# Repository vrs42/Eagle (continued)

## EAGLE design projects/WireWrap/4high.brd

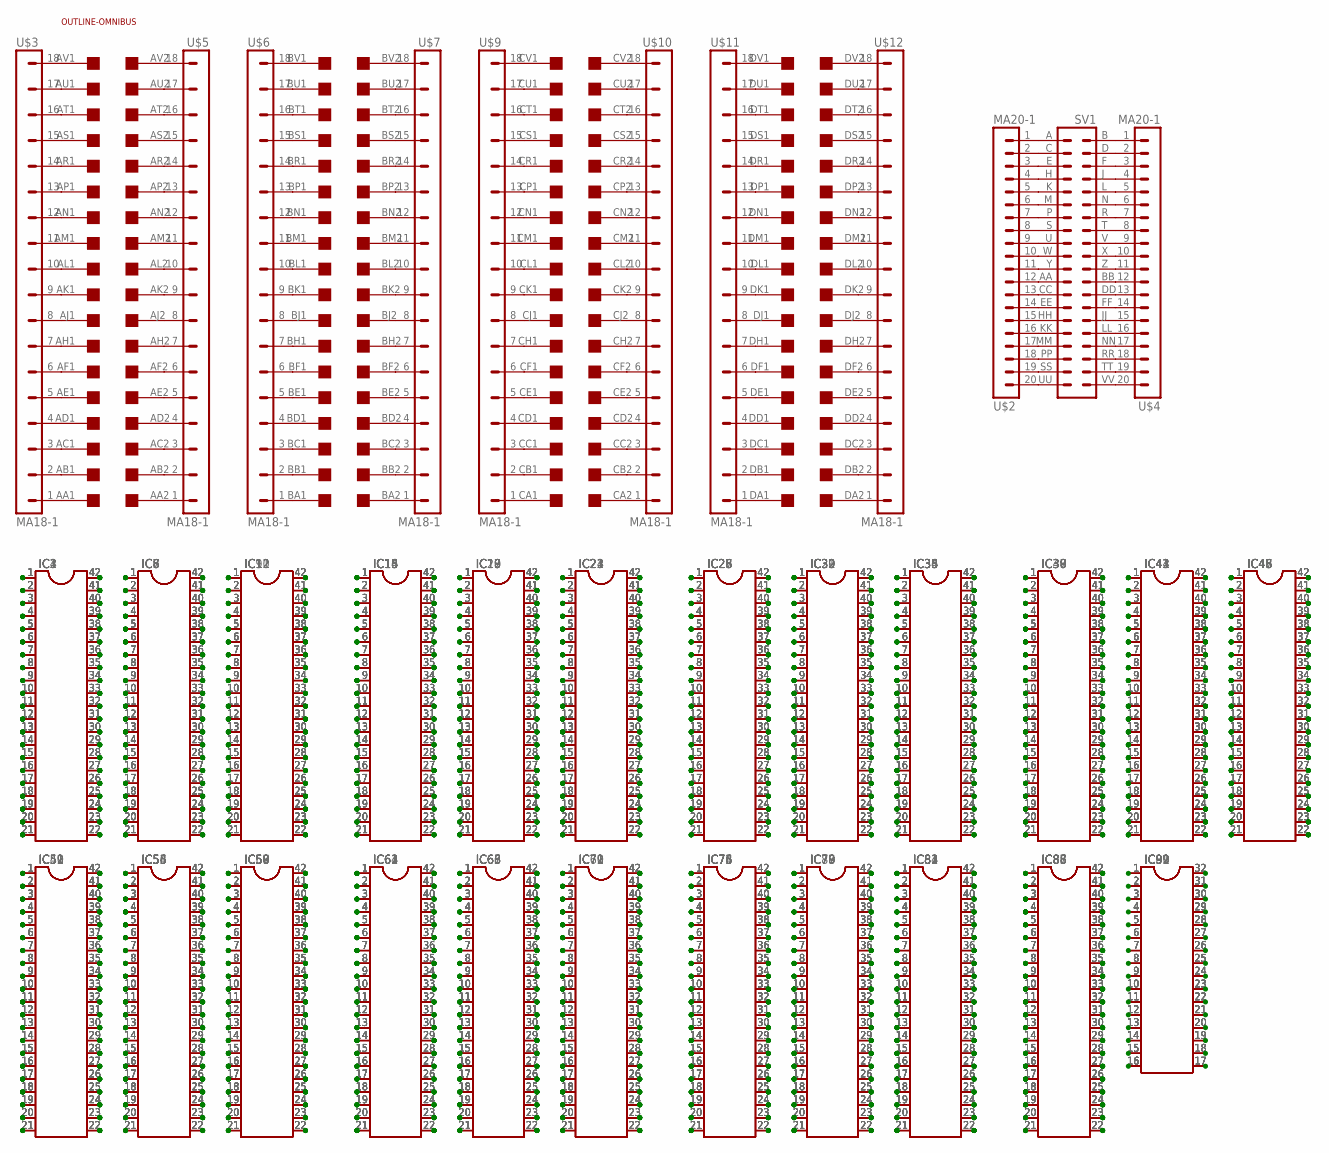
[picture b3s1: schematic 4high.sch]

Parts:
IC1, IC2, IC3, IC4, IC5, IC6, IC7, IC8, IC9, IC10, IC11, IC12, IC13, IC14, IC15, IC16, IC17, IC18, IC19, IC20, IC21, IC22, IC23, IC24, IC25, IC26, IC27, IC28, IC29, IC30, IC31, IC32, IC33, IC34, IC35, IC36, IC37, IC38, IC39, IC40, IC41, IC42, IC43, IC44, IC45, IC46, IC47, IC48, IC49, IC50, IC51, IC52, IC53, IC54, IC55, IC56, IC57, IC58, IC59, IC60, IC61, IC62, IC63, IC64, IC65, IC66, IC67, IC68, IC69, IC70, IC71, IC72, IC73, IC74, IC75, IC76, IC77, IC78, IC79, IC80, IC81, IC82, IC83, IC84, IC85, IC86, IC87, IC88: DIL42
IC89, IC90, IC91, IC92: DIL32
SV1: DEC40PINH
U$1: QUAD; EDGE-CON8
U$2, U$4: MA20-1
U$3, U$5, U$6, U$7, U$9, U$10, U$11, U$12: MA18-1
U$8: OUTLINE-OMNIBUS; OMNIBUS

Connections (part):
GND: U$1.AC2, U$5.3
unnamed: IC1.1, IC2.1, IC3.1, IC4.1
unnamed: IC1.2, IC2.2, IC3.2, IC4.2
unnamed: IC1.3, IC2.3, IC3.3, IC4.3
unnamed: IC1.4, IC2.4, IC3.4, IC4.4
unnamed: IC1.5, IC2.5, IC3.5, IC4.5
unnamed: IC1.6, IC2.6, IC3.6, IC4.6
unnamed: IC1.7, IC2.7, IC3.7, IC4.7
unnamed: IC1.8, IC2.8, IC3.8, IC4.8
unnamed: IC1.9, IC2.9, IC3.9, IC4.9
unnamed: IC1.10, IC2.10, IC3.10, IC4.10
unnamed: IC1.11, IC2.11, IC3.11, IC4.11
unnamed: IC1.12, IC2.12, IC3.12, IC4.12
unnamed: IC1.13, IC2.13, IC3.13, IC4.13
unnamed: IC1.14, IC2.14, IC3.14, IC4.14
unnamed: IC1.15, IC2.15, IC3.15, IC4.15
unnamed: IC1.16, IC2.16, IC3.16, IC4.16
unnamed: IC1.17, IC2.17, IC3.17, IC4.17
unnamed: IC1.18, IC2.18, IC3.18, IC4.18
unnamed: IC1.19, IC2.19, IC3.19, IC4.19
unnamed: IC1.20, IC2.20, IC3.20, IC4.20
unnamed: IC1.21, IC2.21, IC3.21, IC4.21
unnamed: IC1.22, IC2.22, IC3.22, IC4.22
unnamed: IC1.23, IC2.23, IC3.23, IC4.23
unnamed: IC1.24, IC2.24, IC3.24, IC4.24
unnamed: IC1.25, IC2.25, IC3.25, IC4.25
unnamed: IC1.26, IC2.26, IC3.26, IC4.26
unnamed: IC1.27, IC2.27, IC3.27, IC4.27
unnamed: IC1.28, IC2.28, IC3.28, IC4.28
unnamed: IC1.29, IC2.29, IC3.29, IC4.29
unnamed: IC1.30, IC2.30, IC3.30, IC4.30
unnamed: IC1.31, IC2.31, IC3.31, IC4.31
unnamed: IC1.32, IC2.32, IC3.32, IC4.32
unnamed: IC1.33, IC2.33, IC3.33, IC4.33
unnamed: IC1.34, IC2.34, IC3.34, IC4.34
unnamed: IC1.35, IC2.35, IC3.35, IC4.35
unnamed: IC1.36, IC2.36, IC3.36, IC4.36
unnamed: IC1.37, IC2.37, IC3.37, IC4.37
unnamed: IC1.38, IC2.38, IC3.38, IC4.38
unnamed: IC1.39, IC2.39, IC3.39, IC4.39
unnamed: IC1.40, IC2.40, IC3.40, IC4.40
unnamed: IC1.41, IC2.41, IC3.41, IC4.41
unnamed: IC1.42, IC2.42, IC3.42, IC4.42
unnamed: IC5.1, IC6.1, IC7.1, IC8.1
unnamed: IC5.2, IC6.2, IC7.2, IC8.2
unnamed: IC5.3, IC6.3, IC7.3, IC8.3
unnamed: IC5.4, IC6.4, IC7.4, IC8.4
unnamed: IC5.5, IC6.5, IC7.5, IC8.5
unnamed: IC5.6, IC6.6, IC7.6, IC8.6
unnamed: IC5.7, IC6.7, IC7.7, IC8.7
unnamed: IC5.8, IC6.8, IC7.8, IC8.8
unnamed: IC5.9, IC6.9, IC7.9, IC8.9
unnamed: IC5.10, IC6.10, IC7.10, IC8.10
unnamed: IC5.11, IC6.11, IC7.11, IC8.11
unnamed: IC5.12, IC6.12, IC7.12, IC8.12
unnamed: IC5.13, IC6.13, IC7.13, IC8.13
unnamed: IC5.14, IC6.14, IC7.14, IC8.14
unnamed: IC5.15, IC6.15, IC7.15, IC8.15
unnamed: IC5.16, IC6.16, IC7.16, IC8.16
unnamed: IC5.17, IC6.17, IC7.17, IC8.17
unnamed: IC5.18, IC6.18, IC7.18, IC8.18
unnamed: IC5.19, IC6.19, IC7.19, IC8.19
unnamed: IC5.20, IC6.20, IC7.20, IC8.20
unnamed: IC5.21, IC6.21, IC7.21, IC8.21
unnamed: IC5.22, IC6.22, IC7.22, IC8.22
unnamed: IC5.23, IC6.23, IC7.23, IC8.23
unnamed: IC5.24, IC6.24, IC7.24, IC8.24
unnamed: IC5.25, IC6.25, IC7.25, IC8.25
unnamed: IC5.26, IC6.26, IC7.26, IC8.26
unnamed: IC5.27, IC6.27, IC7.27, IC8.27
unnamed: IC5.28, IC6.28, IC7.28, IC8.28
unnamed: IC5.29, IC6.29, IC7.29, IC8.29
unnamed: IC5.30, IC6.30, IC7.30, IC8.30
unnamed: IC5.31, IC6.31, IC7.31, IC8.31
unnamed: IC5.32, IC6.32, IC7.32, IC8.32
unnamed: IC5.33, IC6.33, IC7.33, IC8.33
unnamed: IC5.34, IC6.34, IC7.34, IC8.34
unnamed: IC5.35, IC6.35, IC7.35, IC8.35
unnamed: IC5.36, IC6.36, IC7.36, IC8.36
unnamed: IC5.37, IC6.37, IC7.37, IC8.37
unnamed: IC5.38, IC6.38, IC7.38, IC8.38
unnamed: IC5.39, IC6.39, IC7.39, IC8.39
unnamed: IC5.40, IC6.40, IC7.40, IC8.40
unnamed: IC5.41, IC6.41, IC7.41, IC8.41
unnamed: IC5.42, IC6.42, IC7.42, IC8.42
unnamed: IC9.1, IC10.1, IC11.1, IC12.1
unnamed: IC9.2, IC10.2, IC11.2, IC12.2
unnamed: IC9.3, IC10.3, IC11.3, IC12.3
unnamed: IC9.4, IC10.4, IC11.4, IC12.4
unnamed: IC9.5, IC10.5, IC11.5, IC12.5
unnamed: IC9.6, IC10.6, IC11.6, IC12.6
unnamed: IC9.7, IC10.7, IC11.7, IC12.7
unnamed: IC9.8, IC10.8, IC11.8, IC12.8
unnamed: IC9.9, IC10.9, IC11.9, IC12.9
unnamed: IC9.10, IC10.10, IC11.10, IC12.10
unnamed: IC9.11, IC10.11, IC11.11, IC12.11
unnamed: IC9.12, IC10.12, IC11.12, IC12.12
unnamed: IC9.13, IC10.13, IC11.13, IC12.13
unnamed: IC9.14, IC10.14, IC11.14, IC12.14
unnamed: IC9.15, IC10.15, IC11.15, IC12.15
unnamed: IC9.16, IC10.16, IC11.16, IC12.16
unnamed: IC9.17, IC10.17, IC11.17, IC12.17
unnamed: IC9.18, IC10.18, IC11.18, IC12.18
unnamed: IC9.19, IC10.19, IC11.19, IC12.19
unnamed: IC9.20, IC10.20, IC11.20, IC12.20
unnamed: IC9.21, IC10.21, IC11.21, IC12.21
unnamed: IC9.22, IC10.22, IC11.22, IC12.22
unnamed: IC9.23, IC10.23, IC11.23, IC12.23
unnamed: IC9.24, IC10.24, IC11.24, IC12.24
unnamed: IC9.25, IC10.25, IC11.25, IC12.25
unnamed: IC9.26, IC10.26, IC11.26, IC12.26
unnamed: IC9.27, IC10.27, IC11.27, IC12.27
unnamed: IC9.28, IC10.28, IC11.28, IC12.28
unnamed: IC9.29, IC10.29, IC11.29, IC12.29
unnamed: IC9.30, IC10.30, IC11.30, IC12.30
unnamed: IC9.31, IC10.31, IC11.31, IC12.31
unnamed: IC9.32, IC10.32, IC11.32, IC12.32
unnamed: IC9.33, IC10.33, IC11.33, IC12.33
unnamed: IC9.34, IC10.34, IC11.34, IC12.34
unnamed: IC9.35, IC10.35, IC11.35, IC12.35
unnamed: IC9.36, IC10.36, IC11.36, IC12.36
unnamed: IC9.37, IC10.37, IC11.37, IC12.37
unnamed: IC9.38, IC10.38, IC11.38, IC12.38
unnamed: IC9.39, IC10.39, IC11.39, IC12.39
unnamed: IC9.40, IC10.40, IC11.40, IC12.40
unnamed: IC9.41, IC10.41, IC11.41, IC12.41
unnamed: IC9.42, IC10.42, IC11.42, IC12.42
unnamed: IC13.1, IC14.1, IC15.1, IC16.1
unnamed: IC13.2, IC14.2, IC15.2, IC16.2
unnamed: IC13.3, IC14.3, IC15.3, IC16.3
unnamed: IC13.4, IC14.4, IC15.4, IC16.4
unnamed: IC13.5, IC14.5, IC15.5, IC16.5
unnamed: IC13.6, IC14.6, IC15.6, IC16.6
unnamed: IC13.7, IC14.7, IC15.7, IC16.7
unnamed: IC13.8, IC14.8, IC15.8, IC16.8
unnamed: IC13.9, IC14.9, IC15.9, IC16.9
unnamed: IC13.10, IC14.10, IC15.10, IC16.10
unnamed: IC13.11, IC14.11, IC15.11, IC16.11
unnamed: IC13.12, IC14.12, IC15.12, IC16.12
unnamed: IC13.13, IC14.13, IC15.13, IC16.13
unnamed: IC13.14, IC14.14, IC15.14, IC16.14
unnamed: IC13.15, IC14.15, IC15.15, IC16.15
unnamed: IC13.16, IC14.16, IC15.16, IC16.16
unnamed: IC13.17, IC14.17, IC15.17, IC16.17
unnamed: IC13.18, IC14.18, IC15.18, IC16.18
unnamed: IC13.19, IC14.19, IC15.19, IC16.19
unnamed: IC13.20, IC14.20, IC15.20, IC16.20
unnamed: IC13.21, IC14.21, IC15.21, IC16.21
unnamed: IC13.22, IC14.22, IC15.22, IC16.22
unnamed: IC13.23, IC14.23, IC15.23, IC16.23
unnamed: IC13.24, IC14.24, IC15.24, IC16.24
unnamed: IC13.25, IC14.25, IC15.25, IC16.25
unnamed: IC13.26, IC14.26, IC15.26, IC16.26
unnamed: IC13.27, IC14.27, IC15.27, IC16.27
unnamed: IC13.28, IC14.28, IC15.28, IC16.28
unnamed: IC13.29, IC14.29, IC15.29, IC16.29
unnamed: IC13.30, IC14.30, IC15.30, IC16.30
unnamed: IC13.31, IC14.31, IC15.31, IC16.31
unnamed: IC13.32, IC14.32, IC15.32, IC16.32
unnamed: IC13.33, IC14.33, IC15.33, IC16.33
unnamed: IC13.34, IC14.34, IC15.34, IC16.34
unnamed: IC13.35, IC14.35, IC15.35, IC16.35
unnamed: IC13.36, IC14.36, IC15.36, IC16.36
unnamed: IC13.37, IC14.37, IC15.37, IC16.37
unnamed: IC13.38, IC14.38, IC15.38, IC16.38
unnamed: IC13.39, IC14.39, IC15.39, IC16.39
unnamed: IC13.40, IC14.40, IC15.40, IC16.40
unnamed: IC13.41, IC14.41, IC15.41, IC16.41
unnamed: IC13.42, IC14.42, IC15.42, IC16.42
unnamed: U$1.AK1, U$3.9
unnamed: U$1.AL1, U$3.10
unnamed: U$1.AM1, U$3.11
unnamed: U$1.AN1, U$3.12
unnamed: U$1.AP1, U$3.13
unnamed: U$1.AR1, U$3.14
unnamed: U$1.AS1, U$3.15
unnamed: U$1.AT1, U$3.16
unnamed: U$1.AU1, U$3.17
unnamed: U$1.AV1, U$3.18
unnamed: U$1.AJ1, U$3.8
unnamed: U$1.AH1, U$3.7
unnamed: U$1.AF1, U$3.6
unnamed: U$1.AE1, U$3.5
unnamed: U$1.AD1, U$3.4
unnamed: U$1.AC1, U$3.3
unnamed: U$1.AB1, U$3.2
unnamed: U$1.AA1, U$3.1
unnamed: U$1.AL2, U$5.10
unnamed: U$1.AM2, U$5.11
unnamed: U$1.AN2, U$5.12
unnamed: U$1.AP2, U$5.13
unnamed: U$1.AR2, U$5.14
unnamed: U$1.AS2, U$5.15
unnamed: U$1.AT2, U$5.16
unnamed: U$1.AK2, U$5.9
unnamed: U$1.AJ2, U$5.8
unnamed: U$1.AH2, U$5.7
unnamed: U$1.AF2, U$5.6
unnamed: U$1.AE2, U$5.5
unnamed: U$1.AD2, U$5.4
unnamed: IC17.1, IC18.1, IC19.1, IC20.1
unnamed: U$1.AU2, U$5.17
unnamed: U$1.AV2, U$5.18
unnamed: U$1.AB2, U$5.2
unnamed: IC17.2, IC18.2, IC19.2, IC20.2
unnamed: IC17.3, IC18.3, IC19.3, IC20.3
unnamed: IC17.4, IC18.4, IC19.4, IC20.4
unnamed: IC17.5, IC18.5, IC19.5, IC20.5
unnamed: IC17.6, IC18.6, IC19.6, IC20.6
unnamed: IC17.7, IC18.7, IC19.7, IC20.7
unnamed: IC17.8, IC18.8, IC19.8, IC20.8
unnamed: IC17.9, IC18.9, IC19.9, IC20.9
unnamed: IC17.10, IC18.10, IC19.10, IC20.10
unnamed: IC17.11, IC18.11, IC19.11, IC20.11
unnamed: IC17.12, IC18.12, IC19.12, IC20.12
unnamed: IC17.13, IC18.13, IC19.13, IC20.13
unnamed: IC17.14, IC18.14, IC19.14, IC20.14
unnamed: IC17.15, IC18.15, IC19.15, IC20.15
unnamed: IC17.16, IC18.16, IC19.16, IC20.16
unnamed: IC17.17, IC18.17, IC19.17, IC20.17
unnamed: IC17.18, IC18.18, IC19.18, IC20.18
unnamed: IC17.19, IC18.19, IC19.19, IC20.19
unnamed: IC17.20, IC18.20, IC19.20, IC20.20
unnamed: IC17.21, IC18.21, IC19.21, IC20.21
unnamed: IC17.22, IC18.22, IC19.22, IC20.22
unnamed: IC17.23, IC18.23, IC19.23, IC20.23
unnamed: IC17.24, IC18.24, IC19.24, IC20.24
unnamed: IC17.25, IC18.25, IC19.25, IC20.25
unnamed: IC17.26, IC18.26, IC19.26, IC20.26
unnamed: IC17.27, IC18.27, IC19.27, IC20.27
unnamed: IC17.28, IC18.28, IC19.28, IC20.28
unnamed: IC17.29, IC18.29, IC19.29, IC20.29
unnamed: IC17.30, IC18.30, IC19.30, IC20.30
unnamed: IC17.31, IC18.31, IC19.31, IC20.31
unnamed: IC17.32, IC18.32, IC19.32, IC20.32
unnamed: IC17.33, IC18.33, IC19.33, IC20.33
unnamed: IC17.34, IC18.34, IC19.34, IC20.34
unnamed: IC17.35, IC18.35, IC19.35, IC20.35
unnamed: IC17.36, IC18.36, IC19.36, IC20.36
unnamed: IC17.37, IC18.37, IC19.37, IC20.37
unnamed: IC17.38, IC18.38, IC19.38, IC20.38
unnamed: IC17.39, IC18.39, IC19.39, IC20.39
unnamed: IC17.40, IC18.40, IC19.40, IC20.40
unnamed: IC17.41, IC18.41, IC19.41, IC20.41
unnamed: IC17.42, IC18.42, IC19.42, IC20.42
unnamed: IC21.1, IC22.1, IC23.1, IC24.1
unnamed: IC21.2, IC22.2, IC23.2, IC24.2
unnamed: IC21.3, IC22.3, IC23.3, IC24.3
unnamed: IC21.4, IC22.4, IC23.4, IC24.4
unnamed: IC21.5, IC22.5, IC23.5, IC24.5
unnamed: IC21.6, IC22.6, IC23.6, IC24.6
unnamed: IC21.7, IC22.7, IC23.7, IC24.7
unnamed: IC21.8, IC22.8, IC23.8, IC24.8
unnamed: IC21.9, IC22.9, IC23.9, IC24.9
unnamed: IC21.10, IC22.10, IC23.10, IC24.10
unnamed: IC21.11, IC22.11, IC23.11, IC24.11
unnamed: IC21.12, IC22.12, IC23.12, IC24.12
unnamed: IC21.13, IC22.13, IC23.13, IC24.13
unnamed: IC21.14, IC22.14, IC23.14, IC24.14
unnamed: IC21.15, IC22.15, IC23.15, IC24.15
unnamed: IC21.16, IC22.16, IC23.16, IC24.16
unnamed: IC21.17, IC22.17, IC23.17, IC24.17
unnamed: IC21.18, IC22.18, IC23.18, IC24.18
unnamed: IC21.19, IC22.19, IC23.19, IC24.19
unnamed: IC21.20, IC22.20, IC23.20, IC24.20
unnamed: IC21.21, IC22.21, IC23.21, IC24.21
unnamed: IC21.22, IC22.22, IC23.22, IC24.22
unnamed: IC21.23, IC22.23, IC23.23, IC24.23
unnamed: IC21.24, IC22.24, IC23.24, IC24.24
unnamed: IC21.25, IC22.25, IC23.25, IC24.25
unnamed: IC21.26, IC22.26, IC23.26, IC24.26
unnamed: IC21.27, IC22.27, IC23.27, IC24.27
unnamed: IC21.28, IC22.28, IC23.28, IC24.28
unnamed: IC21.29, IC22.29, IC23.29, IC24.29
unnamed: IC21.30, IC22.30, IC23.30, IC24.30
unnamed: IC21.31, IC22.31, IC23.31, IC24.31
unnamed: IC21.32, IC22.32, IC23.32, IC24.32
unnamed: IC21.33, IC22.33, IC23.33, IC24.33
unnamed: IC21.34, IC22.34, IC23.34, IC24.34
unnamed: IC21.35, IC22.35, IC23.35, IC24.35
unnamed: IC21.36, IC22.36, IC23.36, IC24.36
unnamed: IC21.37, IC22.37, IC23.37, IC24.37
unnamed: IC21.38, IC22.38, IC23.38, IC24.38
unnamed: IC21.39, IC22.39, IC23.39, IC24.39
unnamed: IC21.40, IC22.40, IC23.40, IC24.40
unnamed: IC21.41, IC22.41, IC23.41, IC24.41
unnamed: IC21.42, IC22.42, IC23.42, IC24.42
unnamed: IC25.1, IC26.1, IC27.1, IC28.1
unnamed: IC25.2, IC26.2, IC27.2, IC28.2
unnamed: IC25.3, IC26.3, IC27.3, IC28.3
unnamed: IC25.4, IC26.4, IC27.4, IC28.4
unnamed: IC25.5, IC26.5, IC27.5, IC28.5
unnamed: IC25.6, IC26.6, IC27.6, IC28.6
unnamed: IC25.7, IC26.7, IC27.7, IC28.7
unnamed: IC25.8, IC26.8, IC27.8, IC28.8
unnamed: IC25.9, IC26.9, IC27.9, IC28.9
unnamed: IC25.10, IC26.10, IC27.10, IC28.10
unnamed: IC25.11, IC26.11, IC27.11, IC28.11
unnamed: IC25.12, IC26.12, IC27.12, IC28.12
unnamed: IC25.13, IC26.13, IC27.13, IC28.13
unnamed: IC25.14, IC26.14, IC27.14, IC28.14
unnamed: IC25.15, IC26.15, IC27.15, IC28.15
unnamed: IC25.16, IC26.16, IC27.16, IC28.16
unnamed: IC25.17, IC26.17, IC27.17, IC28.17
unnamed: IC25.18, IC26.18, IC27.18, IC28.18
unnamed: IC25.19, IC26.19, IC27.19, IC28.19
unnamed: IC25.20, IC26.20, IC27.20, IC28.20
unnamed: IC25.21, IC26.21, IC27.21, IC28.21
unnamed: IC25.22, IC26.22, IC27.22, IC28.22
unnamed: IC25.23, IC26.23, IC27.23, IC28.23
unnamed: IC25.24, IC26.24, IC27.24, IC28.24
unnamed: IC25.25, IC26.25, IC27.25, IC28.25
unnamed: IC25.26, IC26.26, IC27.26, IC28.26
unnamed: IC25.27, IC26.27, IC27.27, IC28.27
unnamed: IC25.28, IC26.28, IC27.28, IC28.28
unnamed: IC25.29, IC26.29, IC27.29, IC28.29
unnamed: IC25.30, IC26.30, IC27.30, IC28.30
unnamed: IC25.31, IC26.31, IC27.31, IC28.31
unnamed: IC25.32, IC26.32, IC27.32, IC28.32
unnamed: IC25.33, IC26.33, IC27.33, IC28.33
unnamed: IC25.34, IC26.34, IC27.34, IC28.34
unnamed: IC25.35, IC26.35, IC27.35, IC28.35
unnamed: IC25.36, IC26.36, IC27.36, IC28.36
unnamed: IC25.37, IC26.37, IC27.37, IC28.37
unnamed: IC25.38, IC26.38, IC27.38, IC28.38
unnamed: IC25.39, IC26.39, IC27.39, IC28.39
unnamed: IC25.40, IC26.40, IC27.40, IC28.40
unnamed: IC25.41, IC26.41, IC27.41, IC28.41
unnamed: IC25.42, IC26.42, IC27.42, IC28.42
unnamed: IC29.1, IC30.1, IC31.1, IC32.1
unnamed: IC29.2, IC30.2, IC31.2, IC32.2
unnamed: IC29.3, IC30.3, IC31.3, IC32.3
unnamed: IC29.4, IC30.4, IC31.4, IC32.4
unnamed: IC29.5, IC30.5, IC31.5, IC32.5
unnamed: IC29.6, IC30.6, IC31.6, IC32.6
unnamed: IC29.7, IC30.7, IC31.7, IC32.7
unnamed: IC29.8, IC30.8, IC31.8, IC32.8
unnamed: IC29.9, IC30.9, IC31.9, IC32.9
unnamed: IC29.10, IC30.10, IC31.10, IC32.10
unnamed: IC29.11, IC30.11, IC31.11, IC32.11
unnamed: IC29.12, IC30.12, IC31.12, IC32.12
unnamed: IC29.13, IC30.13, IC31.13, IC32.13
unnamed: IC29.14, IC30.14, IC31.14, IC32.14
unnamed: IC29.15, IC30.15, IC31.15, IC32.15
unnamed: IC29.16, IC30.16, IC31.16, IC32.16
unnamed: IC29.17, IC30.17, IC31.17, IC32.17
unnamed: IC29.18, IC30.18, IC31.18, IC32.18
unnamed: IC29.19, IC30.19, IC31.19, IC32.19
unnamed: IC29.20, IC30.20, IC31.20, IC32.20
unnamed: IC29.21, IC30.21, IC31.21, IC32.21
unnamed: IC29.22, IC30.22, IC31.22, IC32.22
unnamed: IC29.23, IC30.23, IC31.23, IC32.23
unnamed: IC29.24, IC30.24, IC31.24, IC32.24
unnamed: IC29.25, IC30.25, IC31.25, IC32.25
unnamed: IC29.26, IC30.26, IC31.26, IC32.26
unnamed: IC29.27, IC30.27, IC31.27, IC32.27
unnamed: IC29.28, IC30.28, IC31.28, IC32.28
unnamed: IC29.29, IC30.29, IC31.29, IC32.29
unnamed: IC29.30, IC30.30, IC31.30, IC32.30
unnamed: IC29.31, IC30.31, IC31.31, IC32.31
unnamed: IC29.32, IC30.32, IC31.32, IC32.32
unnamed: IC29.33, IC30.33, IC31.33, IC32.33
unnamed: IC29.34, IC30.34, IC31.34, IC32.34
unnamed: IC29.35, IC30.35, IC31.35, IC32.35
unnamed: IC29.36, IC30.36, IC31.36, IC32.36
unnamed: IC29.37, IC30.37, IC31.37, IC32.37
unnamed: IC29.38, IC30.38, IC31.38, IC32.38
unnamed: IC29.39, IC30.39, IC31.39, IC32.39
unnamed: IC29.40, IC30.40, IC31.40, IC32.40
unnamed: IC29.41, IC30.41, IC31.41, IC32.41
unnamed: IC29.42, IC30.42, IC31.42, IC32.42
unnamed: IC33.1, IC34.1, IC35.1, IC36.1
unnamed: IC33.2, IC34.2, IC35.2, IC36.2
unnamed: U$1.BV1, U$6.18
unnamed: U$1.BU1, U$6.17
unnamed: U$1.BT1, U$6.16
unnamed: U$1.BS1, U$6.15
unnamed: U$1.BR1, U$6.14
unnamed: U$1.BP1, U$6.13
unnamed: U$1.BN1, U$6.12
unnamed: U$1.BM1, U$6.11
unnamed: U$1.BL1, U$6.10
unnamed: U$1.BK1, U$6.9
unnamed: U$1.BJ1, U$6.8
unnamed: U$1.BH1, U$6.7
unnamed: U$1.BF1, U$6.6
unnamed: U$1.BE1, U$6.5
unnamed: U$1.BD1, U$6.4
unnamed: U$1.BC1, U$6.3
unnamed: U$1.BB1, U$6.2
unnamed: U$1.BA1, U$6.1
unnamed: U$1.BV2, U$7.18
unnamed: U$1.BU2, U$7.17
unnamed: U$1.BT2, U$7.16
unnamed: U$1.BS2, U$7.15
unnamed: U$1.BR2, U$7.14
unnamed: U$1.BP2, U$7.13
unnamed: U$1.BN2, U$7.12
unnamed: U$1.BM2, U$7.11
unnamed: U$1.BL2, U$7.10
unnamed: U$1.BK2, U$7.9
unnamed: U$1.BJ2, U$7.8
unnamed: U$1.BH2, U$7.7
unnamed: U$1.BF2, U$7.6
unnamed: U$1.BE2, U$7.5
unnamed: U$1.BD2, U$7.4
unnamed: U$1.BC2, U$7.3
unnamed: U$1.BB2, U$7.2
unnamed: U$1.BA2, U$7.1
unnamed: U$1.CV1, U$9.18
unnamed: U$1.CU1, U$9.17
unnamed: U$1.CT1, U$9.16
unnamed: U$1.CS1, U$9.15
unnamed: U$1.CR1, U$9.14
unnamed: U$1.CP1, U$9.13
unnamed: U$1.CN1, U$9.12
unnamed: U$1.CM1, U$9.11
unnamed: U$1.CL1, U$9.10
unnamed: U$1.CK1, U$9.9
unnamed: U$1.CJ1, U$9.8
unnamed: U$1.CH1, U$9.7
unnamed: U$1.CF1, U$9.6
unnamed: U$1.CE1, U$9.5
unnamed: U$1.CD1, U$9.4
unnamed: U$1.CC1, U$9.3
unnamed: U$1.CB1, U$9.2
unnamed: U$1.CA1, U$9.1
unnamed: U$1.CV2, U$10.18
unnamed: U$1.CU2, U$10.17
unnamed: U$1.CT2, U$10.16
unnamed: U$1.CS2, U$10.15
unnamed: U$1.CR2, U$10.14
unnamed: U$1.CP2, U$10.13
unnamed: U$1.CN2, U$10.12
unnamed: U$1.CM2, U$10.11
unnamed: U$1.CL2, U$10.10
unnamed: U$1.CK2, U$10.9
unnamed: U$1.CJ2, U$10.8
unnamed: U$1.CH2, U$10.7
unnamed: U$1.CF2, U$10.6
unnamed: U$1.CE2, U$10.5
unnamed: U$1.CD2, U$10.4
unnamed: U$1.CC2, U$10.3
unnamed: U$1.CB2, U$10.2
unnamed: U$1.CA2, U$10.1
unnamed: U$1.DV1, U$11.18
unnamed: U$1.DU1, U$11.17
unnamed: U$1.DT1, U$11.16
unnamed: U$1.DS1, U$11.15
unnamed: U$1.DR1, U$11.14
unnamed: U$1.DP1, U$11.13
unnamed: U$1.DN1, U$11.12
unnamed: U$1.DM1, U$11.11
unnamed: U$1.DL1, U$11.10
unnamed: U$1.DK1, U$11.9
unnamed: U$1.DJ1, U$11.8
unnamed: U$1.DH1, U$11.7
unnamed: U$1.DF1, U$11.6
unnamed: U$1.DE1, U$11.5
unnamed: U$1.DD1, U$11.4
unnamed: U$1.DC1, U$11.3
unnamed: U$1.DB1, U$11.2
unnamed: U$1.DA1, U$11.1
unnamed: U$1.DV2, U$12.18
unnamed: U$1.DU2, U$12.17
unnamed: U$1.DT2, U$12.16
unnamed: U$1.DS2, U$12.15
unnamed: U$1.DR2, U$12.14
unnamed: U$1.DP2, U$12.13
unnamed: U$1.DN2, U$12.12
unnamed: U$1.DM2, U$12.11
unnamed: U$1.DL2, U$12.10
unnamed: U$1.DK2, U$12.9
unnamed: U$1.DJ2, U$12.8
unnamed: U$1.DH2, U$12.7
unnamed: U$1.DF2, U$12.6
unnamed: U$1.DE2, U$12.5
unnamed: U$1.DD2, U$12.4
unnamed: U$1.DC2, U$12.3
unnamed: U$1.DB2, U$12.2
unnamed: U$1.DA2, U$12.1
unnamed: IC33.3, IC34.3, IC35.3, IC36.3
unnamed: IC33.4, IC34.4, IC35.4, IC36.4
unnamed: IC33.5, IC34.5, IC35.5, IC36.5
unnamed: IC33.6, IC34.6, IC35.6, IC36.6
unnamed: IC33.7, IC34.7, IC35.7, IC36.7
unnamed: IC33.8, IC34.8, IC35.8, IC36.8
unnamed: IC33.9, IC34.9, IC35.9, IC36.9
unnamed: IC33.10, IC34.10, IC35.10, IC36.10
unnamed: IC33.11, IC34.11, IC35.11, IC36.11
unnamed: IC33.12, IC34.12, IC35.12, IC36.12
unnamed: IC33.13, IC34.13, IC35.13, IC36.13
unnamed: IC33.14, IC34.14, IC35.14, IC36.14
unnamed: IC33.15, IC34.15, IC35.15, IC36.15
unnamed: IC33.16, IC34.16, IC35.16, IC36.16
unnamed: IC33.17, IC34.17, IC35.17, IC36.17
unnamed: IC33.18, IC34.18, IC35.18, IC36.18
unnamed: IC33.19, IC34.19, IC35.19, IC36.19
unnamed: IC33.20, IC34.20, IC35.20, IC36.20
unnamed: IC33.21, IC34.21, IC35.21, IC36.21
unnamed: IC33.22, IC34.22, IC35.22, IC36.22
unnamed: IC33.23, IC34.23, IC35.23, IC36.23
unnamed: IC33.24, IC34.24, IC35.24, IC36.24
unnamed: IC33.25, IC34.25, IC35.25, IC36.25
unnamed: IC33.26, IC34.26, IC35.26, IC36.26
unnamed: IC33.27, IC34.27, IC35.27, IC36.27
unnamed: IC33.28, IC34.28, IC35.28, IC36.28
unnamed: IC33.29, IC34.29, IC35.29, IC36.29
unnamed: IC33.30, IC34.30, IC35.30, IC36.30
unnamed: IC33.31, IC34.31, IC35.31, IC36.31
unnamed: IC33.32, IC34.32, IC35.32, IC36.32
unnamed: IC33.33, IC34.33, IC35.33, IC36.33
unnamed: IC33.34, IC34.34, IC35.34, IC36.34
unnamed: IC33.35, IC34.35, IC35.35, IC36.35
unnamed: IC33.36, IC34.36, IC35.36, IC36.36
unnamed: IC33.37, IC34.37, IC35.37, IC36.37
unnamed: IC33.38, IC34.38, IC35.38, IC36.38
unnamed: IC33.39, IC34.39, IC35.39, IC36.39
unnamed: IC33.40, IC34.40, IC35.40, IC36.40
unnamed: IC33.41, IC34.41, IC35.41, IC36.41
unnamed: IC33.42, IC34.42, IC35.42, IC36.42
unnamed: IC37.1, IC38.1, IC39.1, IC40.1
unnamed: IC37.2, IC38.2, IC39.2, IC40.2
unnamed: IC37.3, IC38.3, IC39.3, IC40.3
unnamed: IC37.4, IC38.4, IC39.4, IC40.4
unnamed: IC37.5, IC38.5, IC39.5, IC40.5
unnamed: IC37.6, IC38.6, IC39.6, IC40.6
unnamed: IC37.7, IC38.7, IC39.7, IC40.7
unnamed: IC37.8, IC38.8, IC39.8, IC40.8
unnamed: IC37.9, IC38.9, IC39.9, IC40.9
unnamed: IC37.10, IC38.10, IC39.10, IC40.10
unnamed: IC37.11, IC38.11, IC39.11, IC40.11
unnamed: IC37.12, IC38.12, IC39.12, IC40.12
unnamed: IC37.13, IC38.13, IC39.13, IC40.13
unnamed: IC37.14, IC38.14, IC39.14, IC40.14
unnamed: IC37.15, IC38.15, IC39.15, IC40.15
unnamed: IC37.16, IC38.16, IC39.16, IC40.16
unnamed: IC37.17, IC38.17, IC39.17, IC40.17
unnamed: IC37.18, IC38.18, IC39.18, IC40.18
unnamed: IC37.19, IC38.19, IC39.19, IC40.19
unnamed: IC37.20, IC38.20, IC39.20, IC40.20
unnamed: IC37.21, IC38.21, IC39.21, IC40.21
unnamed: IC37.22, IC38.22, IC39.22, IC40.22
unnamed: IC37.23, IC38.23, IC39.23, IC40.23
unnamed: IC37.24, IC38.24, IC39.24, IC40.24
unnamed: IC37.25, IC38.25, IC39.25, IC40.25
unnamed: IC37.26, IC38.26, IC39.26, IC40.26
unnamed: IC37.27, IC38.27, IC39.27, IC40.27
unnamed: IC37.28, IC38.28, IC39.28, IC40.28
unnamed: IC37.29, IC38.29, IC39.29, IC40.29
unnamed: IC37.30, IC38.30, IC39.30, IC40.30
unnamed: IC37.31, IC38.31, IC39.31, IC40.31
unnamed: IC37.32, IC38.32, IC39.32, IC40.32
unnamed: IC37.33, IC38.33, IC39.33, IC40.33
unnamed: IC37.34, IC38.34, IC39.34, IC40.34
unnamed: IC37.35, IC38.35, IC39.35, IC40.35
unnamed: IC37.36, IC38.36, IC39.36, IC40.36
unnamed: IC37.37, IC38.37, IC39.37, IC40.37
unnamed: IC37.38, IC38.38, IC39.38, IC40.38
unnamed: IC37.39, IC38.39, IC39.39, IC40.39
unnamed: IC37.40, IC38.40, IC39.40, IC40.40
unnamed: IC37.41, IC38.41, IC39.41, IC40.41
unnamed: IC37.42, IC38.42, IC39.42, IC40.42
unnamed: IC41.1, IC42.1, IC43.1, IC44.1
unnamed: IC41.2, IC42.2, IC43.2, IC44.2
unnamed: IC41.3, IC42.3, IC43.3, IC44.3
unnamed: IC41.4, IC42.4, IC43.4, IC44.4
unnamed: IC41.5, IC42.5, IC43.5, IC44.5
unnamed: IC41.6, IC42.6, IC43.6, IC44.6
unnamed: IC41.7, IC42.7, IC43.7, IC44.7
unnamed: IC41.8, IC42.8, IC43.8, IC44.8
unnamed: IC41.9, IC42.9, IC43.9, IC44.9
unnamed: IC41.10, IC42.10, IC43.10, IC44.10
unnamed: IC41.11, IC42.11, IC43.11, IC44.11
unnamed: IC41.12, IC42.12, IC43.12, IC44.12
unnamed: IC41.13, IC42.13, IC43.13, IC44.13
unnamed: IC41.14, IC42.14, IC43.14, IC44.14
unnamed: IC41.15, IC42.15, IC43.15, IC44.15
unnamed: IC41.16, IC42.16, IC43.16, IC44.16
unnamed: IC41.17, IC42.17, IC43.17, IC44.17
unnamed: IC41.18, IC42.18, IC43.18, IC44.18
unnamed: IC41.19, IC42.19, IC43.19, IC44.19
unnamed: IC41.20, IC42.20, IC43.20, IC44.20
unnamed: IC41.21, IC42.21, IC43.21, IC44.21
unnamed: IC41.22, IC42.22, IC43.22, IC44.22
unnamed: IC41.23, IC42.23, IC43.23, IC44.23
unnamed: IC41.24, IC42.24, IC43.24, IC44.24
unnamed: IC41.25, IC42.25, IC43.25, IC44.25
unnamed: IC41.26, IC42.26, IC43.26, IC44.26
unnamed: IC41.27, IC42.27, IC43.27, IC44.27
unnamed: IC41.28, IC42.28, IC43.28, IC44.28
unnamed: IC41.29, IC42.29, IC43.29, IC44.29
unnamed: IC41.30, IC42.30, IC43.30, IC44.30
unnamed: IC41.31, IC42.31, IC43.31, IC44.31
unnamed: IC41.32, IC42.32, IC43.32, IC44.32
unnamed: IC41.33, IC42.33, IC43.33, IC44.33
unnamed: IC41.34, IC42.34, IC43.34, IC44.34
unnamed: IC41.35, IC42.35, IC43.35, IC44.35
unnamed: IC41.36, IC42.36, IC43.36, IC44.36
unnamed: IC41.37, IC42.37, IC43.37, IC44.37
unnamed: IC41.38, IC42.38, IC43.38, IC44.38
unnamed: IC41.39, IC42.39, IC43.39, IC44.39
unnamed: IC41.40, IC42.40, IC43.40, IC44.40
unnamed: IC41.41, IC42.41, IC43.41, IC44.41
unnamed: IC41.42, IC42.42, IC43.42, IC44.42
unnamed: IC45.1, IC46.1, IC47.1, IC48.1
unnamed: IC45.2, IC46.2, IC47.2, IC48.2
unnamed: IC45.3, IC46.3, IC47.3, IC48.3
unnamed: IC45.4, IC46.4, IC47.4, IC48.4
unnamed: IC45.5, IC46.5, IC47.5, IC48.5
unnamed: IC45.6, IC46.6, IC47.6, IC48.6
unnamed: IC45.7, IC46.7, IC47.7, IC48.7
unnamed: IC45.8, IC46.8, IC47.8, IC48.8
unnamed: IC45.9, IC46.9, IC47.9, IC48.9
unnamed: IC45.10, IC46.10, IC47.10, IC48.10
unnamed: IC45.11, IC46.11, IC47.11, IC48.11
unnamed: IC45.12, IC46.12, IC47.12, IC48.12
unnamed: IC45.13, IC46.13, IC47.13, IC48.13
unnamed: IC45.14, IC46.14, IC47.14, IC48.14
unnamed: IC45.15, IC46.15, IC47.15, IC48.15
unnamed: IC45.16, IC46.16, IC47.16, IC48.16
unnamed: IC45.17, IC46.17, IC47.17, IC48.17
unnamed: IC45.18, IC46.18, IC47.18, IC48.18
unnamed: IC45.19, IC46.19, IC47.19, IC48.19
unnamed: IC45.20, IC46.20, IC47.20, IC48.20
unnamed: IC45.21, IC46.21, IC47.21, IC48.21
unnamed: IC45.22, IC46.22, IC47.22, IC48.22
unnamed: IC45.23, IC46.23, IC47.23, IC48.23
unnamed: IC45.24, IC46.24, IC47.24, IC48.24
unnamed: IC45.25, IC46.25, IC47.25, IC48.25
unnamed: IC45.26, IC46.26, IC47.26, IC48.26
unnamed: IC45.27, IC46.27, IC47.27, IC48.27
unnamed: IC45.28, IC46.28, IC47.28, IC48.28
unnamed: IC45.29, IC46.29, IC47.29, IC48.29
unnamed: IC45.30, IC46.30, IC47.30, IC48.30
unnamed: IC45.31, IC46.31, IC47.31, IC48.31
unnamed: IC45.32, IC46.32, IC47.32, IC48.32
unnamed: IC45.33, IC46.33, IC47.33, IC48.33
unnamed: IC45.34, IC46.34, IC47.34, IC48.34
unnamed: IC45.35, IC46.35, IC47.35, IC48.35
unnamed: IC45.36, IC46.36, IC47.36, IC48.36
unnamed: IC45.37, IC46.37, IC47.37, IC48.37
unnamed: IC45.38, IC46.38, IC47.38, IC48.38
unnamed: IC45.39, IC46.39, IC47.39, IC48.39
unnamed: IC45.40, IC46.40, IC47.40, IC48.40
unnamed: IC45.41, IC46.41, IC47.41, IC48.41
unnamed: IC45.42, IC46.42, IC47.42, IC48.42
unnamed: IC49.1, IC50.1, IC51.1, IC52.1
unnamed: IC49.2, IC50.2, IC51.2, IC52.2
unnamed: IC49.3, IC50.3, IC51.3, IC52.3
unnamed: IC49.4, IC50.4, IC51.4, IC52.4
unnamed: IC49.5, IC50.5, IC51.5, IC52.5
unnamed: IC49.6, IC50.6, IC51.6, IC52.6
unnamed: IC49.7, IC50.7, IC51.7, IC52.7
unnamed: IC49.8, IC50.8, IC51.8, IC52.8
unnamed: IC49.9, IC50.9, IC51.9, IC52.9
unnamed: IC49.10, IC50.10, IC51.10, IC52.10
unnamed: IC49.11, IC50.11, IC51.11, IC52.11
unnamed: IC49.12, IC50.12, IC51.12, IC52.12
unnamed: IC49.13, IC50.13, IC51.13, IC52.13
unnamed: IC49.14, IC50.14, IC51.14, IC52.14
unnamed: IC49.15, IC50.15, IC51.15, IC52.15
unnamed: IC49.16, IC50.16, IC51.16, IC52.16
unnamed: IC49.17, IC50.17, IC51.17, IC52.17
unnamed: IC49.18, IC50.18, IC51.18, IC52.18
unnamed: IC49.19, IC50.19, IC51.19, IC52.19
unnamed: IC49.20, IC50.20, IC51.20, IC52.20
unnamed: IC49.21, IC50.21, IC51.21, IC52.21
unnamed: IC49.22, IC50.22, IC51.22, IC52.22
unnamed: IC49.23, IC50.23, IC51.23, IC52.23
unnamed: IC49.24, IC50.24, IC51.24, IC52.24
unnamed: IC49.25, IC50.25, IC51.25, IC52.25
unnamed: IC49.26, IC50.26, IC51.26, IC52.26
unnamed: IC49.27, IC50.27, IC51.27, IC52.27
unnamed: IC49.28, IC50.28, IC51.28, IC52.28
unnamed: IC49.29, IC50.29, IC51.29, IC52.29
unnamed: IC49.30, IC50.30, IC51.30, IC52.30
unnamed: IC49.31, IC50.31, IC51.31, IC52.31
unnamed: IC49.32, IC50.32, IC51.32, IC52.32
unnamed: IC49.33, IC50.33, IC51.33, IC52.33
unnamed: IC49.34, IC50.34, IC51.34, IC52.34
unnamed: IC49.35, IC50.35, IC51.35, IC52.35
unnamed: IC49.36, IC50.36, IC51.36, IC52.36
unnamed: IC49.37, IC50.37, IC51.37, IC52.37
unnamed: IC49.38, IC50.38, IC51.38, IC52.38
unnamed: IC49.39, IC50.39, IC51.39, IC52.39
unnamed: IC49.40, IC50.40, IC51.40, IC52.40
unnamed: IC49.41, IC50.41, IC51.41, IC52.41
unnamed: IC49.42, IC50.42, IC51.42, IC52.42
unnamed: IC53.1, IC54.1, IC55.1, IC56.1
unnamed: IC53.2, IC54.2, IC55.2, IC56.2
unnamed: IC53.3, IC54.3, IC55.3, IC56.3
unnamed: IC53.4, IC54.4, IC55.4, IC56.4
unnamed: IC53.5, IC54.5, IC55.5, IC56.5
unnamed: IC53.6, IC54.6, IC55.6, IC56.6
unnamed: IC53.7, IC54.7, IC55.7, IC56.7
unnamed: IC53.8, IC54.8, IC55.8, IC56.8
unnamed: IC53.9, IC54.9, IC55.9, IC56.9
unnamed: IC53.10, IC54.10, IC55.10, IC56.10
unnamed: IC53.11, IC54.11, IC55.11, IC56.11
unnamed: IC53.12, IC54.12, IC55.12, IC56.12
unnamed: IC53.13, IC54.13, IC55.13, IC56.13
unnamed: IC53.14, IC54.14, IC55.14, IC56.14
unnamed: IC53.15, IC54.15, IC55.15, IC56.15
unnamed: IC53.16, IC54.16, IC55.16, IC56.16
unnamed: IC53.17, IC54.17, IC55.17, IC56.17
unnamed: IC53.18, IC54.18, IC55.18, IC56.18
unnamed: IC53.19, IC54.19, IC55.19, IC56.19
unnamed: IC53.20, IC54.20, IC55.20, IC56.20
unnamed: IC53.21, IC54.21, IC55.21, IC56.21
unnamed: IC53.22, IC54.22, IC55.22, IC56.22
unnamed: IC53.23, IC54.23, IC55.23, IC56.23
unnamed: IC53.24, IC54.24, IC55.24, IC56.24
unnamed: IC53.25, IC54.25, IC55.25, IC56.25
unnamed: IC53.26, IC54.26, IC55.26, IC56.26
unnamed: IC53.27, IC54.27, IC55.27, IC56.27
unnamed: IC53.28, IC54.28, IC55.28, IC56.28
unnamed: IC53.29, IC54.29, IC55.29, IC56.29
unnamed: IC53.30, IC54.30, IC55.30, IC56.30
unnamed: IC53.31, IC54.31, IC55.31, IC56.31
unnamed: IC53.32, IC54.32, IC55.32, IC56.32
unnamed: IC53.33, IC54.33, IC55.33, IC56.33
unnamed: IC53.34, IC54.34, IC55.34, IC56.34
unnamed: IC53.35, IC54.35, IC55.35, IC56.35
unnamed: IC53.36, IC54.36, IC55.36, IC56.36
unnamed: IC53.37, IC54.37, IC55.37, IC56.37
unnamed: IC53.38, IC54.38, IC55.38, IC56.38
unnamed: IC53.39, IC54.39, IC55.39, IC56.39
unnamed: IC53.40, IC54.40, IC55.40, IC56.40
unnamed: IC53.41, IC54.41, IC55.41, IC56.41
unnamed: IC53.42, IC54.42, IC55.42, IC56.42
unnamed: IC57.1, IC58.1, IC59.1, IC60.1
unnamed: IC57.2, IC58.2, IC59.2, IC60.2
unnamed: IC57.3, IC58.3, IC59.3, IC60.3
unnamed: IC57.4, IC58.4, IC59.4, IC60.4
unnamed: IC57.5, IC58.5, IC59.5, IC60.5
unnamed: IC57.6, IC58.6, IC59.6, IC60.6
unnamed: IC57.7, IC58.7, IC59.7, IC60.7
unnamed: IC57.8, IC58.8, IC59.8, IC60.8
unnamed: IC57.9, IC58.9, IC59.9, IC60.9
unnamed: IC57.10, IC58.10, IC59.10, IC60.10
unnamed: IC57.11, IC58.11, IC59.11, IC60.11
unnamed: IC57.12, IC58.12, IC59.12, IC60.12
unnamed: IC57.13, IC58.13, IC59.13, IC60.13
unnamed: IC57.14, IC58.14, IC59.14, IC60.14
unnamed: IC57.15, IC58.15, IC59.15, IC60.15
unnamed: IC57.16, IC58.16, IC59.16, IC60.16
unnamed: IC57.17, IC58.17, IC59.17, IC60.17
unnamed: IC57.18, IC58.18, IC59.18, IC60.18
unnamed: IC57.19, IC58.19, IC59.19, IC60.19
unnamed: IC57.20, IC58.20, IC59.20, IC60.20
unnamed: IC57.21, IC58.21, IC59.21, IC60.21
unnamed: IC57.22, IC58.22, IC59.22, IC60.22
unnamed: IC57.23, IC58.23, IC59.23, IC60.23
unnamed: IC57.24, IC58.24, IC59.24, IC60.24
unnamed: IC57.25, IC58.25, IC59.25, IC60.25
unnamed: IC57.26, IC58.26, IC59.26, IC60.26
unnamed: IC57.27, IC58.27, IC59.27, IC60.27
unnamed: IC57.28, IC58.28, IC59.28, IC60.28
unnamed: IC57.29, IC58.29, IC59.29, IC60.29
unnamed: IC57.30, IC58.30, IC59.30, IC60.30
unnamed: IC57.31, IC58.31, IC59.31, IC60.31
unnamed: IC57.32, IC58.32, IC59.32, IC60.32
unnamed: IC57.33, IC58.33, IC59.33, IC60.33
unnamed: IC57.34, IC58.34, IC59.34, IC60.34
unnamed: IC57.35, IC58.35, IC59.35, IC60.35
unnamed: IC57.36, IC58.36, IC59.36, IC60.36
unnamed: IC57.37, IC58.37, IC59.37, IC60.37
unnamed: IC57.38, IC58.38, IC59.38, IC60.38
unnamed: IC57.39, IC58.39, IC59.39, IC60.39
unnamed: IC57.40, IC58.40, IC59.40, IC60.40
unnamed: IC57.41, IC58.41, IC59.41, IC60.41
unnamed: IC57.42, IC58.42, IC59.42, IC60.42
unnamed: IC61.1, IC62.1, IC63.1, IC64.1
unnamed: IC61.2, IC62.2, IC63.2, IC64.2
unnamed: IC61.3, IC62.3, IC63.3, IC64.3
unnamed: IC61.4, IC62.4, IC63.4, IC64.4
unnamed: IC61.5, IC62.5, IC63.5, IC64.5
unnamed: IC61.6, IC62.6, IC63.6, IC64.6
unnamed: IC61.7, IC62.7, IC63.7, IC64.7
unnamed: IC61.8, IC62.8, IC63.8, IC64.8
unnamed: IC61.9, IC62.9, IC63.9, IC64.9
unnamed: IC61.10, IC62.10, IC63.10, IC64.10
unnamed: IC61.11, IC62.11, IC63.11, IC64.11
unnamed: IC61.12, IC62.12, IC63.12, IC64.12
unnamed: IC61.13, IC62.13, IC63.13, IC64.13
unnamed: IC61.14, IC62.14, IC63.14, IC64.14
unnamed: IC61.15, IC62.15, IC63.15, IC64.15
unnamed: IC61.16, IC62.16, IC63.16, IC64.16
unnamed: IC61.17, IC62.17, IC63.17, IC64.17
unnamed: IC61.18, IC62.18, IC63.18, IC64.18
unnamed: IC61.19, IC62.19, IC63.19, IC64.19
unnamed: IC61.20, IC62.20, IC63.20, IC64.20
unnamed: IC61.21, IC62.21, IC63.21, IC64.21
unnamed: IC61.22, IC62.22, IC63.22, IC64.22
unnamed: IC61.23, IC62.23, IC63.23, IC64.23
unnamed: IC61.24, IC62.24, IC63.24, IC64.24
unnamed: IC61.25, IC62.25, IC63.25, IC64.25
unnamed: IC61.26, IC62.26, IC63.26, IC64.26
unnamed: IC61.27, IC62.27, IC63.27, IC64.27
unnamed: IC61.28, IC62.28, IC63.28, IC64.28
unnamed: IC61.29, IC62.29, IC63.29, IC64.29
unnamed: IC61.30, IC62.30, IC63.30, IC64.30
unnamed: IC61.31, IC62.31, IC63.31, IC64.31
unnamed: IC61.32, IC62.32, IC63.32, IC64.32
unnamed: IC61.33, IC62.33, IC63.33, IC64.33
unnamed: IC61.34, IC62.34, IC63.34, IC64.34
unnamed: IC61.35, IC62.35, IC63.35, IC64.35
unnamed: IC61.36, IC62.36, IC63.36, IC64.36
unnamed: IC61.37, IC62.37, IC63.37, IC64.37
unnamed: IC61.38, IC62.38, IC63.38, IC64.38
unnamed: IC61.39, IC62.39, IC63.39, IC64.39
unnamed: IC61.40, IC62.40, IC63.40, IC64.40
unnamed: IC61.41, IC62.41, IC63.41, IC64.41
unnamed: IC61.42, IC62.42, IC63.42, IC64.42
unnamed: IC65.1, IC66.1, IC67.1, IC68.1
unnamed: IC65.2, IC66.2, IC67.2, IC68.2
unnamed: IC65.3, IC66.3, IC67.3, IC68.3
unnamed: IC65.4, IC66.4, IC67.4, IC68.4
unnamed: IC65.5, IC66.5, IC67.5, IC68.5
unnamed: IC65.6, IC66.6, IC67.6, IC68.6
unnamed: IC65.7, IC66.7, IC67.7, IC68.7
unnamed: IC65.8, IC66.8, IC67.8, IC68.8
unnamed: IC65.9, IC66.9, IC67.9, IC68.9
unnamed: IC65.10, IC66.10, IC67.10, IC68.10
unnamed: IC65.11, IC66.11, IC67.11, IC68.11
unnamed: IC65.12, IC66.12, IC67.12, IC68.12
unnamed: IC65.13, IC66.13, IC67.13, IC68.13
unnamed: IC65.14, IC66.14, IC67.14, IC68.14
unnamed: IC65.15, IC66.15, IC67.15, IC68.15
unnamed: IC65.16, IC66.16, IC67.16, IC68.16
unnamed: IC65.17, IC66.17, IC67.17, IC68.17
unnamed: IC65.18, IC66.18, IC67.18, IC68.18
unnamed: IC65.19, IC66.19, IC67.19, IC68.19
unnamed: IC65.20, IC66.20, IC67.20, IC68.20
unnamed: IC65.21, IC66.21, IC67.21, IC68.21
unnamed: IC65.22, IC66.22, IC67.22, IC68.22
unnamed: IC65.23, IC66.23, IC67.23, IC68.23
unnamed: IC65.24, IC66.24, IC67.24, IC68.24
unnamed: IC65.25, IC66.25, IC67.25, IC68.25
unnamed: IC65.26, IC66.26, IC67.26, IC68.26
unnamed: IC65.27, IC66.27, IC67.27, IC68.27
unnamed: IC65.28, IC66.28, IC67.28, IC68.28
unnamed: IC65.29, IC66.29, IC67.29, IC68.29
unnamed: IC65.30, IC66.30, IC67.30, IC68.30
unnamed: IC65.31, IC66.31, IC67.31, IC68.31
unnamed: IC65.32, IC66.32, IC67.32, IC68.32
unnamed: IC65.33, IC66.33, IC67.33, IC68.33
unnamed: IC65.34, IC66.34, IC67.34, IC68.34
unnamed: IC65.35, IC66.35, IC67.35, IC68.35
unnamed: IC65.36, IC66.36, IC67.36, IC68.36
unnamed: IC65.37, IC66.37, IC67.37, IC68.37
unnamed: IC65.38, IC66.38, IC67.38, IC68.38
unnamed: IC65.39, IC66.39, IC67.39, IC68.39
unnamed: IC65.40, IC66.40, IC67.40, IC68.40
unnamed: IC65.41, IC66.41, IC67.41, IC68.41
unnamed: IC65.42, IC66.42, IC67.42, IC68.42
unnamed: IC69.1, IC70.1, IC71.1, IC72.1
unnamed: IC69.2, IC70.2, IC71.2, IC72.2
unnamed: IC69.3, IC70.3, IC71.3, IC72.3
unnamed: IC69.4, IC70.4, IC71.4, IC72.4
unnamed: IC69.5, IC70.5, IC71.5, IC72.5
unnamed: IC69.6, IC70.6, IC71.6, IC72.6
unnamed: IC69.7, IC70.7, IC71.7, IC72.7
unnamed: IC69.8, IC70.8, IC71.8, IC72.8
unnamed: IC69.9, IC70.9, IC71.9, IC72.9
unnamed: IC69.10, IC70.10, IC71.10, IC72.10
unnamed: IC69.11, IC70.11, IC71.11, IC72.11
unnamed: IC69.12, IC70.12, IC71.12, IC72.12
unnamed: IC69.13, IC70.13, IC71.13, IC72.13
unnamed: IC69.14, IC70.14, IC71.14, IC72.14
unnamed: IC69.15, IC70.15, IC71.15, IC72.15
unnamed: IC69.16, IC70.16, IC71.16, IC72.16
unnamed: IC69.17, IC70.17, IC71.17, IC72.17
unnamed: IC69.18, IC70.18, IC71.18, IC72.18
unnamed: IC69.19, IC70.19, IC71.19, IC72.19
unnamed: IC69.20, IC70.20, IC71.20, IC72.20
unnamed: IC69.21, IC70.21, IC71.21, IC72.21
unnamed: IC69.22, IC70.22, IC71.22, IC72.22
unnamed: IC69.23, IC70.23, IC71.23, IC72.23
unnamed: IC69.24, IC70.24, IC71.24, IC72.24
unnamed: IC69.25, IC70.25, IC71.25, IC72.25
unnamed: IC69.26, IC70.26, IC71.26, IC72.26
unnamed: IC69.27, IC70.27, IC71.27, IC72.27
unnamed: IC69.28, IC70.28, IC71.28, IC72.28
unnamed: IC69.29, IC70.29, IC71.29, IC72.29
unnamed: IC69.30, IC70.30, IC71.30, IC72.30
unnamed: IC69.31, IC70.31, IC71.31, IC72.31
unnamed: IC69.32, IC70.32, IC71.32, IC72.32
unnamed: IC69.33, IC70.33, IC71.33, IC72.33
unnamed: IC69.34, IC70.34, IC71.34, IC72.34
unnamed: IC69.35, IC70.35, IC71.35, IC72.35
unnamed: IC69.36, IC70.36, IC71.36, IC72.36
unnamed: IC69.37, IC70.37, IC71.37, IC72.37
unnamed: IC69.38, IC70.38, IC71.38, IC72.38
unnamed: IC69.39, IC70.39, IC71.39, IC72.39
unnamed: IC69.40, IC70.40, IC71.40, IC72.40
unnamed: IC69.41, IC70.41, IC71.41, IC72.41
unnamed: IC69.42, IC70.42, IC71.42, IC72.42
unnamed: IC73.1, IC74.1, IC75.1, IC76.1
unnamed: IC73.2, IC74.2, IC75.2, IC76.2
unnamed: IC73.3, IC74.3, IC75.3, IC76.3
unnamed: IC73.4, IC74.4, IC75.4, IC76.4
unnamed: IC73.5, IC74.5, IC75.5, IC76.5
unnamed: IC73.6, IC74.6, IC75.6, IC76.6
unnamed: IC73.7, IC74.7, IC75.7, IC76.7
unnamed: IC73.8, IC74.8, IC75.8, IC76.8
unnamed: IC73.9, IC74.9, IC75.9, IC76.9
unnamed: IC73.10, IC74.10, IC75.10, IC76.10
unnamed: IC73.11, IC74.11, IC75.11, IC76.11
unnamed: IC73.12, IC74.12, IC75.12, IC76.12
unnamed: IC73.13, IC74.13, IC75.13, IC76.13
unnamed: IC73.14, IC74.14, IC75.14, IC76.14
unnamed: IC73.15, IC74.15, IC75.15, IC76.15
unnamed: IC73.16, IC74.16, IC75.16, IC76.16
unnamed: IC73.17, IC74.17, IC75.17, IC76.17
unnamed: IC73.18, IC74.18, IC75.18, IC76.18
unnamed: IC73.19, IC74.19, IC75.19, IC76.19
unnamed: IC73.20, IC74.20, IC75.20, IC76.20
unnamed: IC73.21, IC74.21, IC75.21, IC76.21
unnamed: IC73.22, IC74.22, IC75.22, IC76.22
unnamed: IC73.23, IC74.23, IC75.23, IC76.23
unnamed: IC73.24, IC74.24, IC75.24, IC76.24
unnamed: IC73.25, IC74.25, IC75.25, IC76.25
unnamed: IC73.26, IC74.26, IC75.26, IC76.26
unnamed: IC73.27, IC74.27, IC75.27, IC76.27
unnamed: IC73.28, IC74.28, IC75.28, IC76.28
unnamed: IC73.29, IC74.29, IC75.29, IC76.29
unnamed: IC73.30, IC74.30, IC75.30, IC76.30
unnamed: IC73.31, IC74.31, IC75.31, IC76.31
unnamed: IC73.32, IC74.32, IC75.32, IC76.32
unnamed: IC73.33, IC74.33, IC75.33, IC76.33
unnamed: IC73.34, IC74.34, IC75.34, IC76.34
unnamed: IC73.35, IC74.35, IC75.35, IC76.35
unnamed: IC73.36, IC74.36, IC75.36, IC76.36
unnamed: IC73.37, IC74.37, IC75.37, IC76.37
unnamed: IC73.38, IC74.38, IC75.38, IC76.38
unnamed: IC73.39, IC74.39, IC75.39, IC76.39
unnamed: IC73.40, IC74.40, IC75.40, IC76.40
unnamed: IC73.41, IC74.41, IC75.41, IC76.41
unnamed: IC73.42, IC74.42, IC75.42, IC76.42
unnamed: IC77.1, IC78.1, IC79.1, IC80.1
unnamed: IC77.2, IC78.2, IC79.2, IC80.2
unnamed: IC77.3, IC78.3, IC79.3, IC80.3
unnamed: IC77.4, IC78.4, IC79.4, IC80.4
unnamed: IC77.5, IC78.5, IC79.5, IC80.5
unnamed: IC77.6, IC78.6, IC79.6, IC80.6
unnamed: IC77.7, IC78.7, IC79.7, IC80.7
unnamed: IC77.8, IC78.8, IC79.8, IC80.8
unnamed: IC77.9, IC78.9, IC79.9, IC80.9
unnamed: IC77.10, IC78.10, IC79.10, IC80.10
unnamed: IC77.11, IC78.11, IC79.11, IC80.11
unnamed: IC77.12, IC78.12, IC79.12, IC80.12
unnamed: IC77.13, IC78.13, IC79.13, IC80.13
unnamed: IC77.14, IC78.14, IC79.14, IC80.14
unnamed: IC77.15, IC78.15, IC79.15, IC80.15
unnamed: IC77.16, IC78.16, IC79.16, IC80.16
unnamed: IC77.17, IC78.17, IC79.17, IC80.17
unnamed: IC77.18, IC78.18, IC79.18, IC80.18
unnamed: IC77.19, IC78.19, IC79.19, IC80.19
unnamed: IC77.20, IC78.20, IC79.20, IC80.20
unnamed: IC77.21, IC78.21, IC79.21, IC80.21
unnamed: IC77.22, IC78.22, IC79.22, IC80.22
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
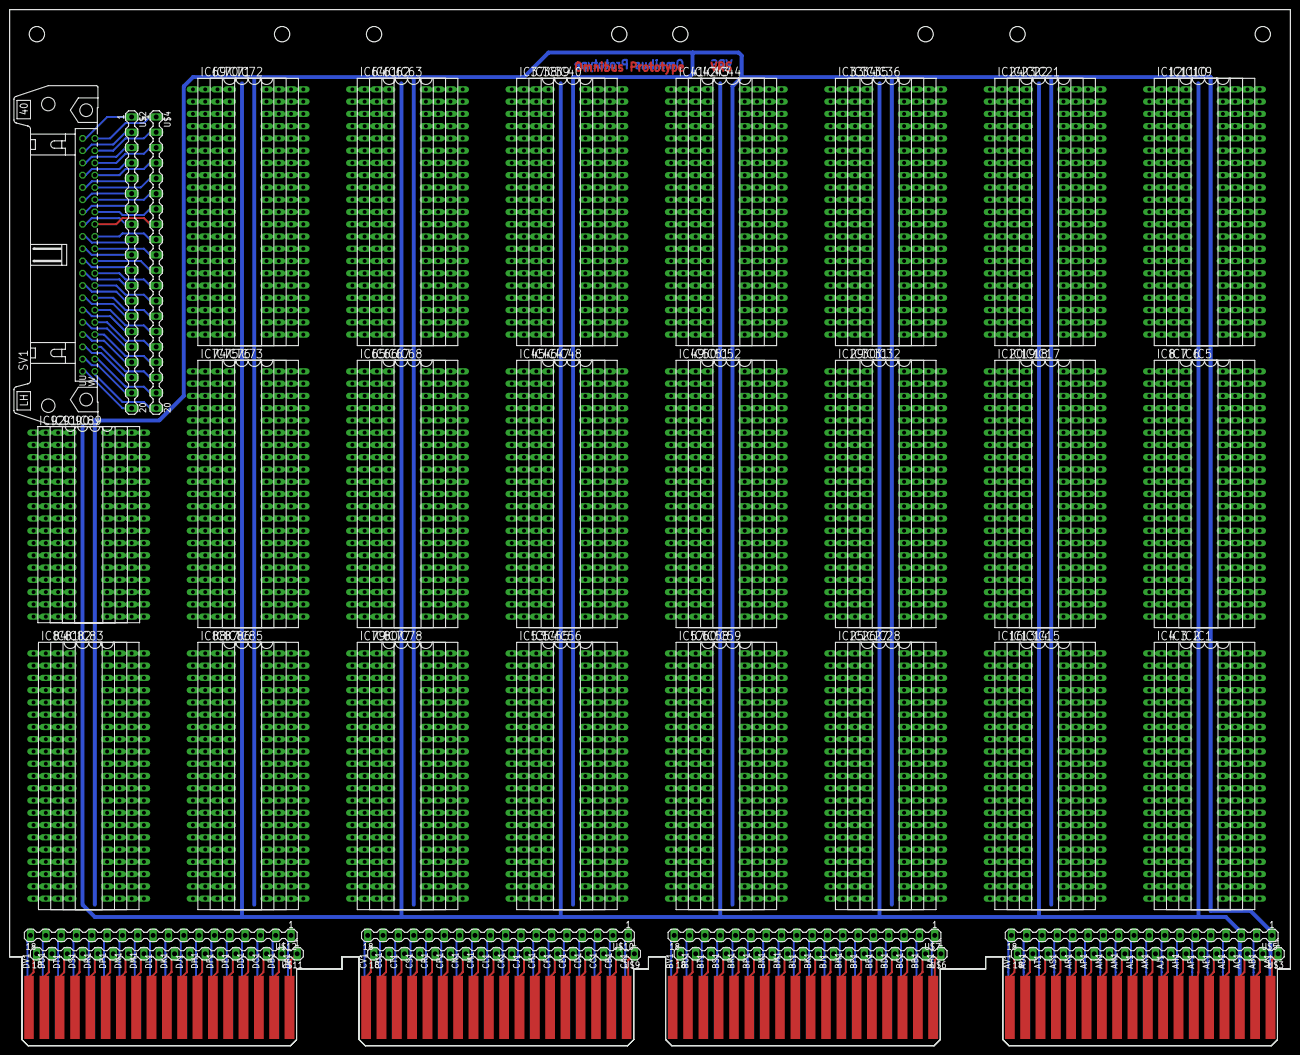
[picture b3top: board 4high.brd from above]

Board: 2 copper layers, 265.3 x 214.6 mm, 105 parts (0 on the bottom side), 1140 nets.
